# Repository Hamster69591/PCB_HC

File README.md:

# PCB_HC
 
- Battery:BatteryHolder_Keystone_3034_1x20mm
- LED_THT:LED_D5.0mm
- Connector_PinHeader_2.54mm:PinHeader_1x02_P2.54mm_Vertical
- Package_TO_SOT_THT:TO-92_Inline
- Resistor_THT:R_Axial_DIN0207_L6.3mm_D2.5mm_P7.62mm_Horizontal
- Potentiometer_THT:Potentiometer_Vishay_T73YP_Vertical
- Button_Switch_THT:SW_PUSH_6mm

Slack Username: Maximilian

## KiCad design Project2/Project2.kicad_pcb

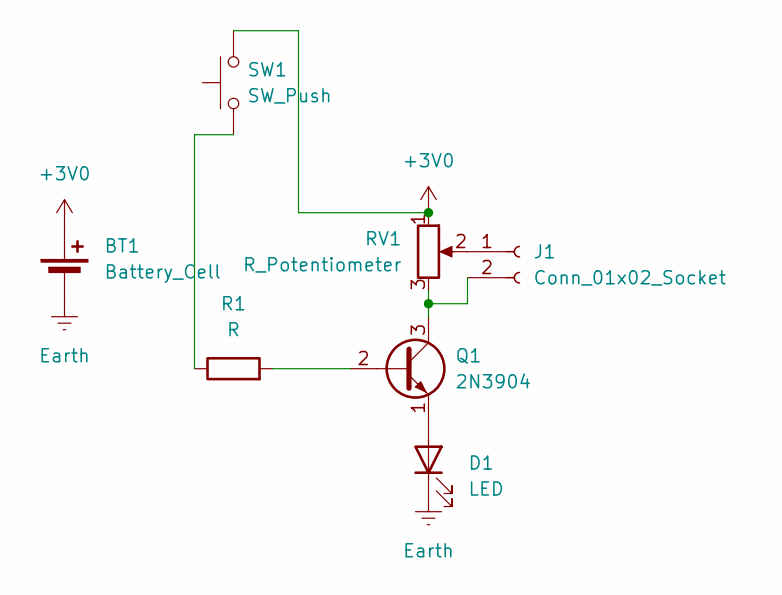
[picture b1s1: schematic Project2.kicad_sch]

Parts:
BT1: Battery_Cell; BatteryHolder_Keystone_3034_1x20mm
D1: LED; LED_D5.0mm
J1: Conn_01x02_Socket; PinHeader_1x02_P2.54mm_Vertical
Q1: 2N3904; TO-92_Inline
R1: R; R_Axial_DIN0207_L6.3mm_D2.5mm_P7.62mm_Horizontal
RV1: R_Potentiometer; Potentiometer_Vishay_T73YP_Vertical
SW1: SW_Push; SW_PUSH_6mm

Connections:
+3V0: BT1.1 (+), RV1.1, SW1.2
Earth: BT1.2 (-), D1.1 (K)
unnamed: D1.2 (A), Q1.1 (E)
unnamed: J1.1, RV1.2
unnamed: J1.2, Q1.3 (C), RV1.3
unnamed: Q1.2 (B), R1.2
unnamed: R1.1, SW1.1

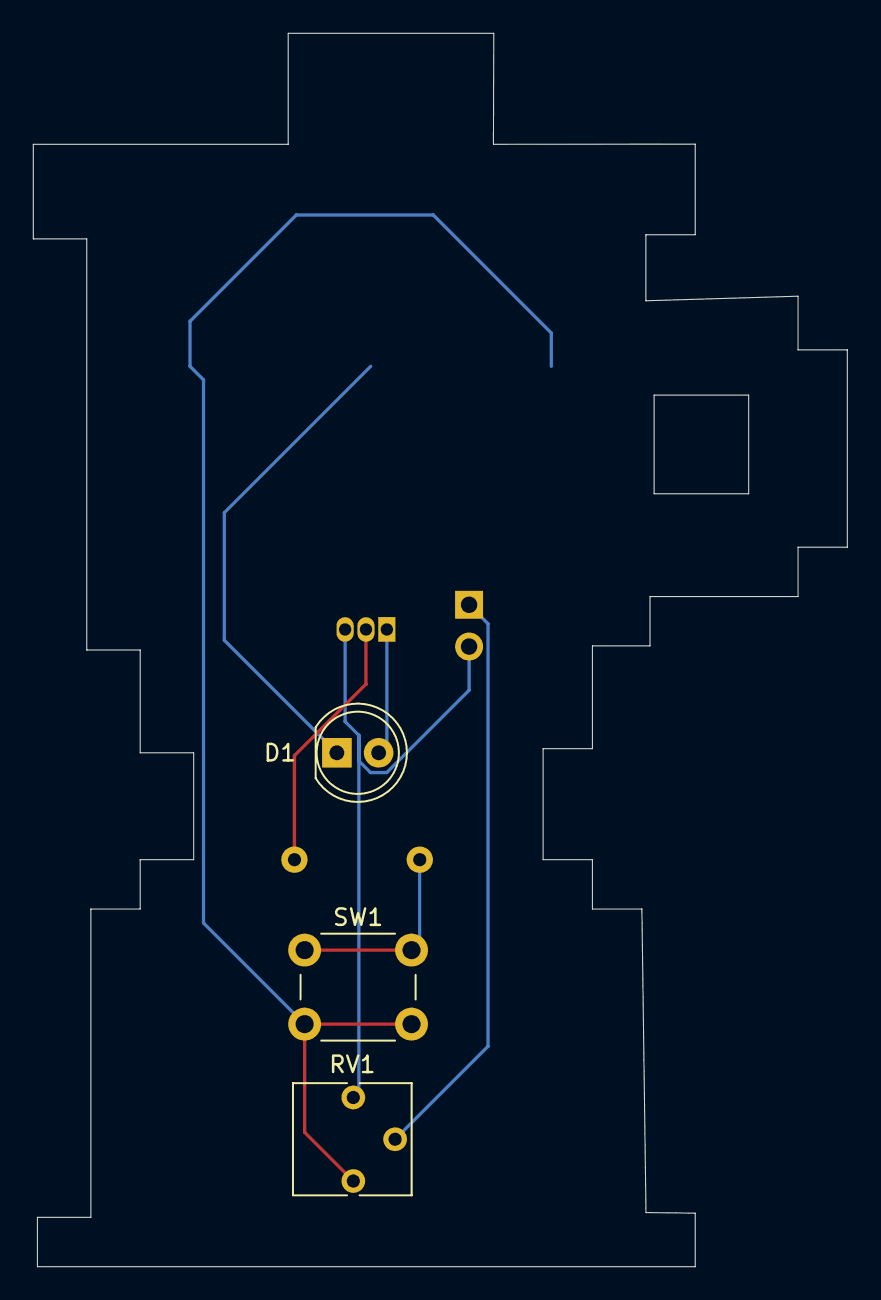
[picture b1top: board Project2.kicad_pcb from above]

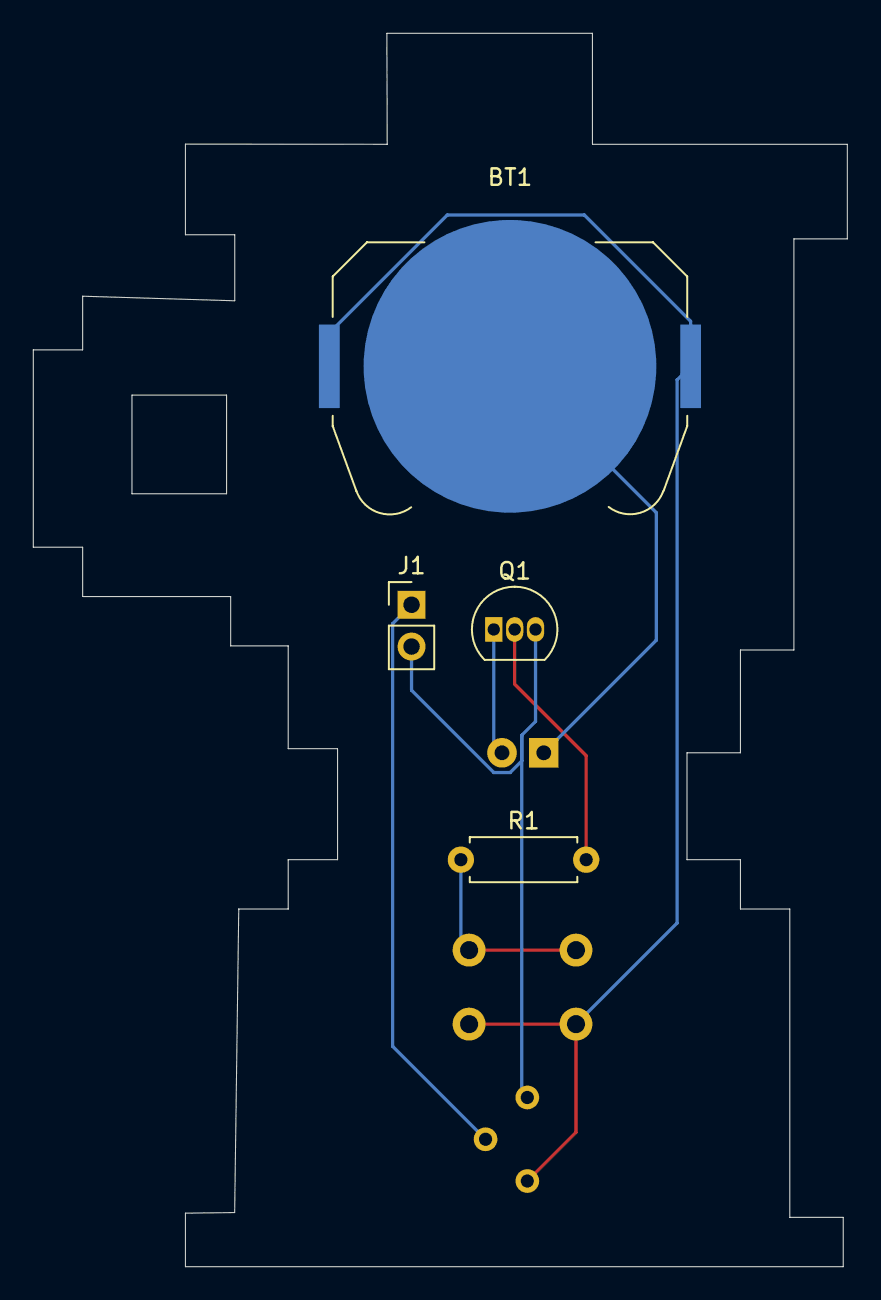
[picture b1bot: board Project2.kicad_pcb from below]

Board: 2 copper layers, 49.5 x 75.0 mm, 7 parts (4 on the bottom side), 7 nets.
